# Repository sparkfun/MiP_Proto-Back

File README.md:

MiP_Proto-Pack
==============

Prototyping board for the MiP by WowWee

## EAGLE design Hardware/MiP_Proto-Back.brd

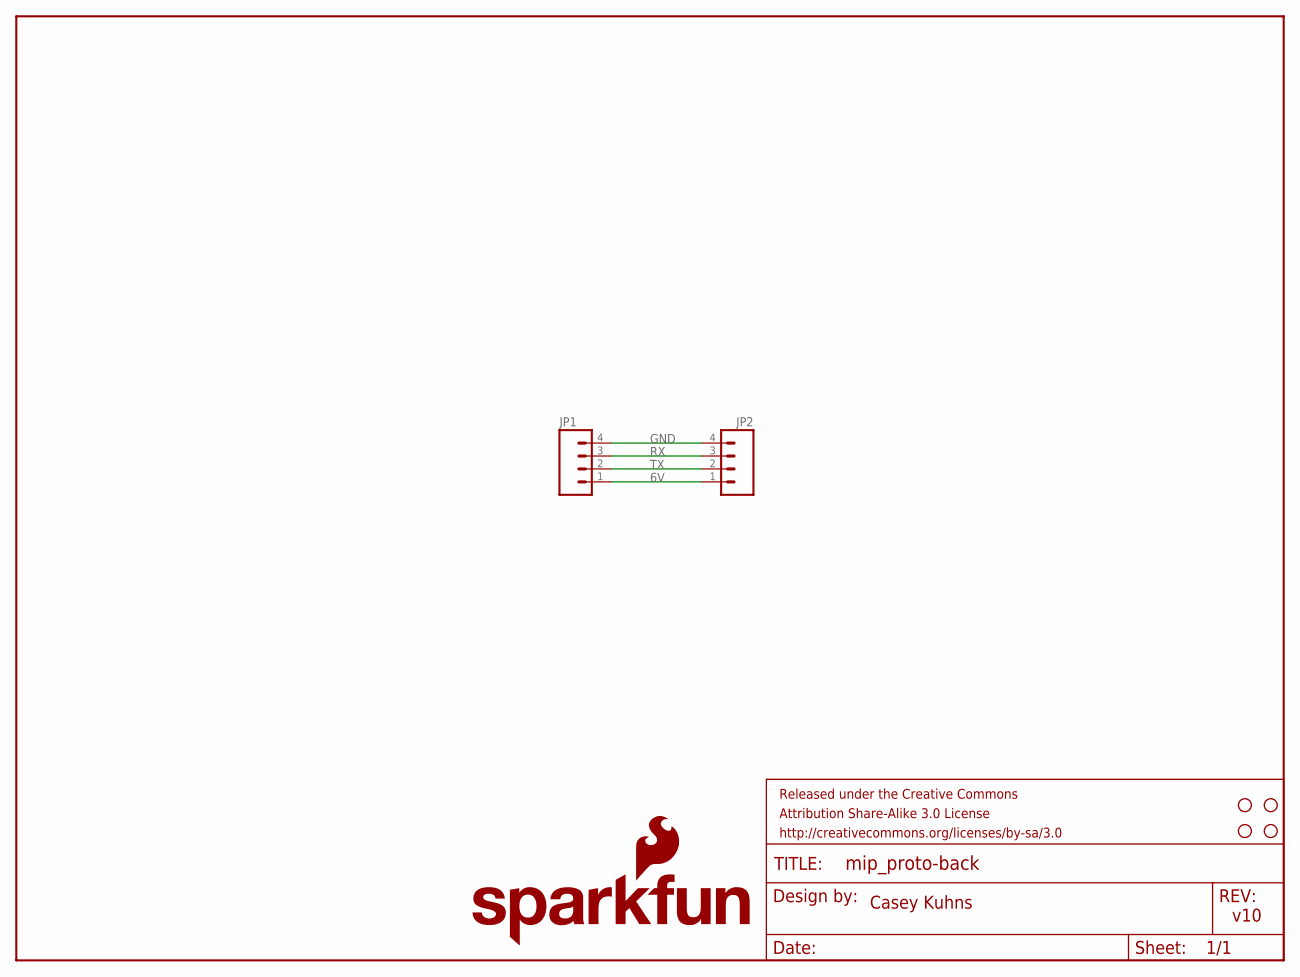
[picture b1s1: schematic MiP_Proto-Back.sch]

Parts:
FRAME1: FRAME-LETTER; CREATIVE_COMMONS
JP1: M04JST; 1X04-1.5MM_JST
JP2: M04PTH; 1X04
LOGO1: SFE_LOGO_NAME_FLAME.2_INCH; SFE_LOGO_NAME_FLAME_.2
STANDOFF1, STANDOFF2, STANDOFF3, STANDOFF4: STAND-OFF

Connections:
6V: JP1.1, JP2.1
GND: JP1.4, JP2.4
RX: JP1.3, JP2.3
TX: JP1.2, JP2.2

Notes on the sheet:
Casey Kuhns
v10

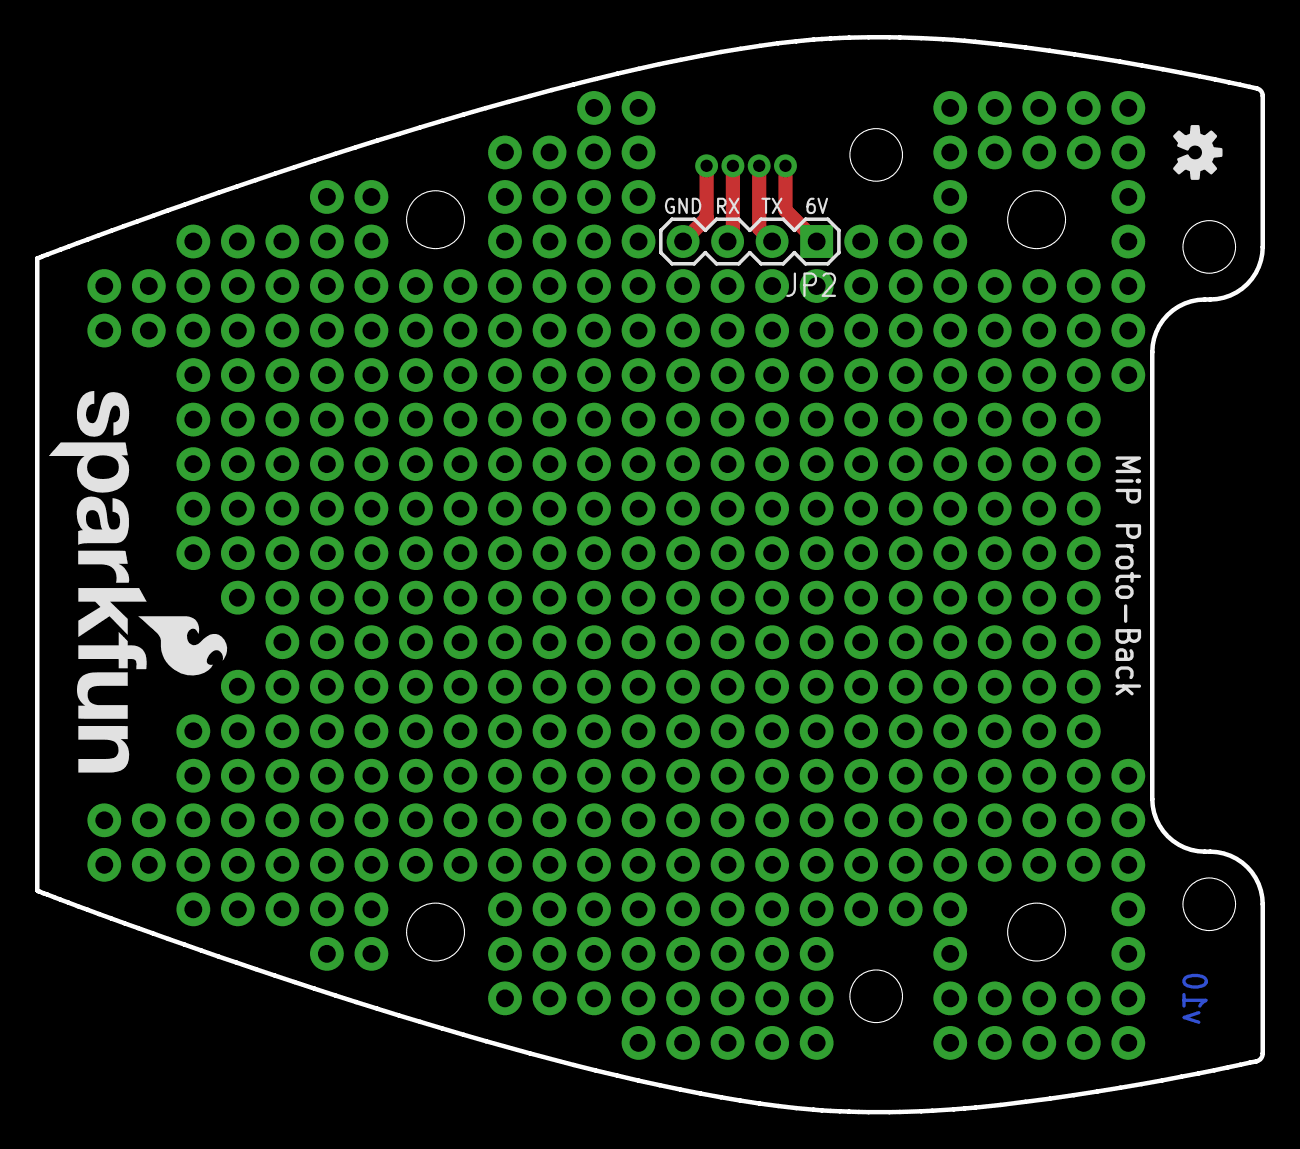
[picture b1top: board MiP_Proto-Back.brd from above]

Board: 2 copper layers, 69.9 x 61.3 mm, 9 parts (1 on the bottom side), 4 nets.

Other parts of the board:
LOGO2: OSHW-LOGOS; OSHW-LOGO-S

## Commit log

2014-08-19 ready for review
2014-08-20 fixed air wire
2014-10-06 changed rev numbers, added name to PCB.
2014-10-06 corrected name

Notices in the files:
parts and their libraries:
SparkFun-Aesthetics: Licensing: CC v3.0 Share-Alike You are welcome to use this library for commercial purposes.
SparkFun-Aesthetics: Released under the Creative Commons Attribution Share-Alike 3.0 License
SparkFun-Aesthetics: http://creativecommons.org/licenses/by-sa/3.0
